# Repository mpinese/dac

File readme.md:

# Note

This project is still under active design, and is not yet completed! Do not build it expecting a functional device... yet.

# An (Almost) No Compromise USB Stereo DAC

This project describes the hardware and firmware for a high-quality DIY USB stereo digital to analogue converter (DAC) with optional integrated digital volume control and headphone amplifier.

## Background

I was after a DAC for my computer headphone setup. Seeing as I enjoy a bit of DIY hardware, I thought to have a go at designing the ideal DAC for me. This would be a high-quality but fairly compact single-box DAC, with integrated preamp and headphone amplifier. If stereo line out and digital (eg S/PDIF in) could be included with minimal effort that would be a bonus.

## Design philosophy

The design is balanced towards maximum audio quality while hopefully avoiding audiophile silliness. Close attention is paid to performance of the key components, gain structure, power rails, stability, and transfer characteristics in the 20-20kHz spectrum. However, you won't see esoteric components, valves, absurdly overspecified linear power supplies / space heaters, etc.

Key principles in the design were:
1. Use asynchronous mode USB audio. I want the PC to have as little influence as possible on the audio playback.
2. Keep the signal digital for as long as possible. For example, perform volume control digitally, rather than using an analogue attenuation stage, which can introduce issues with rolloff and noise.
3. Maintain a simple and clean analog signal path, ideally DC-coupled.
4. Have a solid justification for each design decision; try and avoid reflexive overkill approaches.
5. Where suitable, source components from the [JLCPCB SMT parts library](https://jlcpcb.com/parts/componentSearch). This is a practical and cost-saving measure that is well-worth it for non-critical things like pull-up resistors and decoupling caps.
6. Keep cost under control. Only use high-cost components if lower-cost alternatives are unsuitable.

I would have liked to add '0. Test everything, remove anything unnecessary' but unfortuantely I do not have the kind of test equipment needed to really challenge the design. Therefore some design choices, for example the supply decoupling or separate PSU enclosure, feel a bit over-the-top and can probably be optimised.

## Architecture

```
                                     Panel controls
                                           |
                                           v
                                     +--- MCU ---+
                                     |           |
                                     v           v
  Computer  -->  USB to I2S  -->  Receiver -->  DAC  -->  I2V  -->  Amplifier  -->  Headphones
                                  and ASRC                 |
                                     ^                     v
                                     |                  Line out
                                 Digital in            (3.472 Vpp)
```

* USB to I2S: [Amanero module](https://amanero.com/). A well-established solution for asynchronous USB to I2S conversion. I considered adopting a DIY approach for this stage, but there's no way I could replicate the Amanero's functionality without an investment of effort that far exceeds the cost of the module.
* Clock: Onboard 24.576 MHz oscillator driving both the ASRC and the DAC. The Amanero MCLK output is not used. Simulations indicated that the Kyocera ### is good enough here, and that the popular Crystek CHD series crystal, which has better specs but costs 10X more, is overkill.
* Receiver and ASRC: SRC4392, converting input to fs=96 kHz. This stage also performs digital volume control / attenuation if required.
* DAC: PCM1792A running at fs=96 kHz, with slow rolloff reconstruction filter.
* I2V: Op-amp based, standard Philips architecture of dual transimpedance amplifiers followed by a difference stage. OPA1612 devices for minimum noise. Gain flat within 0.1 dB 20 Hz to 20 kHz. Phase linear within 5 deg to 20 kHz (group delay < 0.1 ms). Total noise < 700 nV RMS (20 Hz - 20 kHz), equivalent to -125 dB relative to +4 dBu output level.
* Amplifier: OPA1612 + LME49600 buffer in feedback loop, unity gain (therefore maximum output level is 3.472 Vpp, matching the line out). AC-coupled input to avoid headphone damage in the case of DC signal, -3 dB at 7.7 Hz, -0.6 dB at 20 Hz, -0.1 dB at 50 Hz and higher; group delay 2.6 ms at 20 Hz, < 0.5 ms at 50 Hz and higher.  Somewhat overkill: characterised down to 16 ohm headphones, stable for all reasonable capacitances, and should be capable of driving any dynamic headphone or IEM out there.
* MCU: STM8S003F3P
* PSU: Switchmode modules for analog and digital supplies, in an external enclosure with LC filtering. In the main DAC enclosure, TPS7A linear postregulators for analog rails.

## Capabilities

* USB input: 
* Digital input: 
* Headphone output: 

## Options

The design is modular and modules can be left out to cut costs or change functionality.  The main modules are:

### Core DAC: essential

This is the only required module.  It performs USB --> stereo analog conversion.

#### Line out startup mute: optional

This module mutes the stereo output while the power rails are unstable (eg during startup).  It prevents the "thump" noise that can often happen when switching the DAC on or off.  However this may not be required in some configurations.

To disable this module, leave out components: 

### Volume control: optional (though highly recommended if headphones are used)

To disable this module, bridge ###

### Headphone amplifier: optional

Components: 

#### Headphone startup mute: optional

Components: 

## Licence

Hardware designs (schematics, PCB layouts, and enclosure plans), software, and documentation are licensed for reuse under the Creative Commons Attribution 4.0 Licence (CC BY 4.0). For more details on this licence, visit https://creativecommons.org/licenses/by/4.0/.

Component models (3D and 2D) under the design/pcbs/lib directory, and simulation models (`*.s*p`, `*.lib`, `*.tld`, `*.TSM` under the simulations directory) remain the property of their creators and are not covered by this CC BY 4.0 licence.

The Kicad BOM template bom2grouped_csv_jlcpcb.xsl was created bt arturo182, see https://gist.github.com/arturo182/a8c4a4b96907cfccf616a1edb59d0389.

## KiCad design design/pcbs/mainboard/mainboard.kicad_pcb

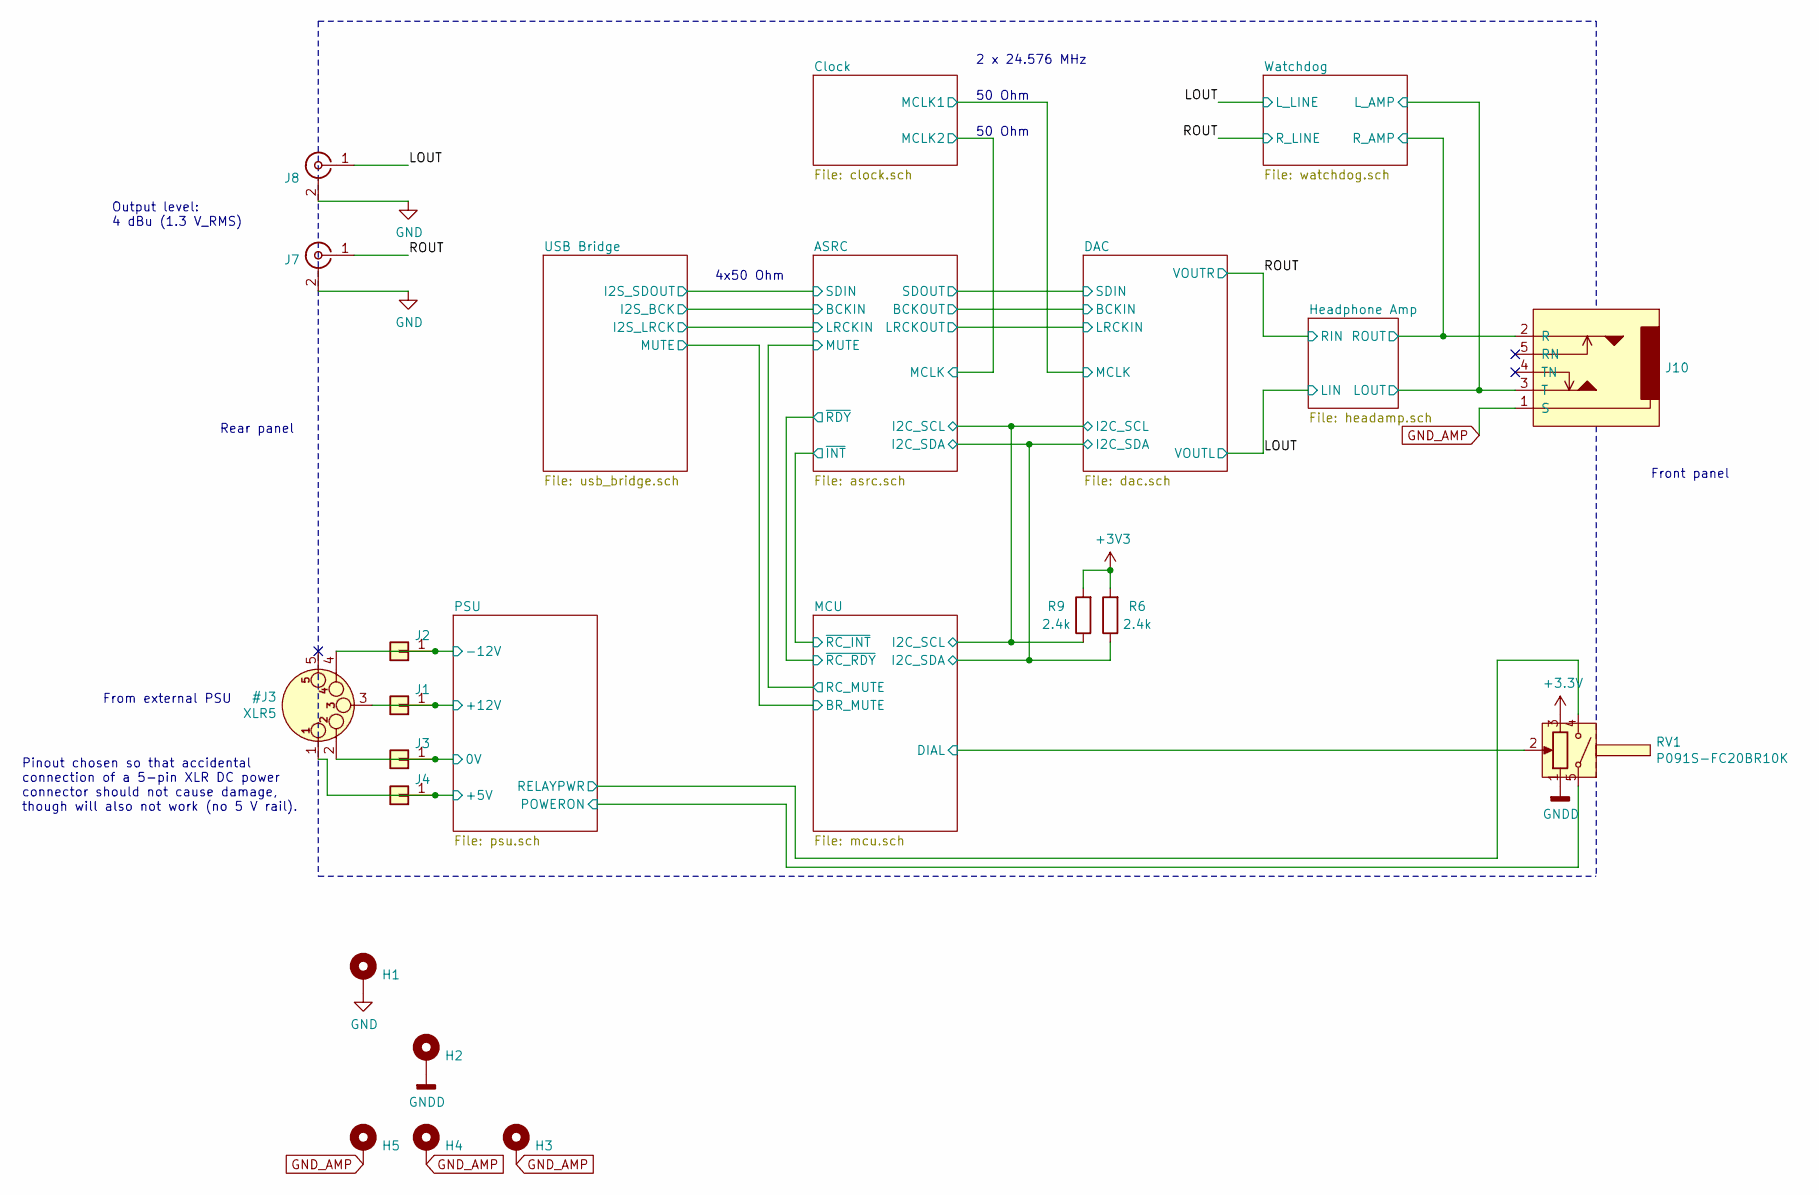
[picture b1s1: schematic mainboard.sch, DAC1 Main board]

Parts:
H1, H2, H3, H4, H5: MountingHole; MountingHole_3.2mm_M3_Pad_Via
J1, J2, J3, J4: Conn_01x01; SolderWirePad_1x01_Drill1.5mm
J7: Conn_Coaxial; SolderWirePad_1x02_P5.08mm_Drill1.5mm; DigiKey SC1828-ND
J8: Conn_Coaxial; SolderWirePad_1x02_P5.08mm_Drill1.5mm; DigiKey SC2440-ND
J10: AudioJackSw; Amphenol_ACJS-MHOM; DigiKey 889-1818-ND
R6, R9: 2.4k; R_0402_1005Metric; LCSC C25882
RV1: P091S-FC20BR10K; DigiKey 987-1283-ND

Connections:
/ASRC/I2C_SCL: R9.1; also elsewhere on the board
/ASRC/I2C_SDA: R6.1; also elsewhere on the board
/Headphone Amp/LOUT: J10.3 (T); also elsewhere on the board
/Headphone Amp/ROUT: J10.2 (R); also elsewhere on the board
/LOUT: J8.1 (In); also elsewhere on the board
/MCU/DIAL: RV1.2; also elsewhere on the board
/PSU/POWERON: RV1.5; also elsewhere on the board
/ROUT: J7.1 (In); also elsewhere on the board
GNDD: H2.1, RV1.1; also elsewhere on the board
GND_AMP: H3.1, H4.1, H5.1, J10.1 (S), J10.6 (S); also elsewhere on the board

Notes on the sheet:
50 Ohm
2 x 24.576 MHz
From external PSU
Rear panel
Front panel
Pinout chosen so that accidental connection of a 5-pin XLR DC power connector should not cause damage, though will also not work (no 5 V rail).
Output level: 4 dBu (1.3 V_RMS)
4x50 Ohm

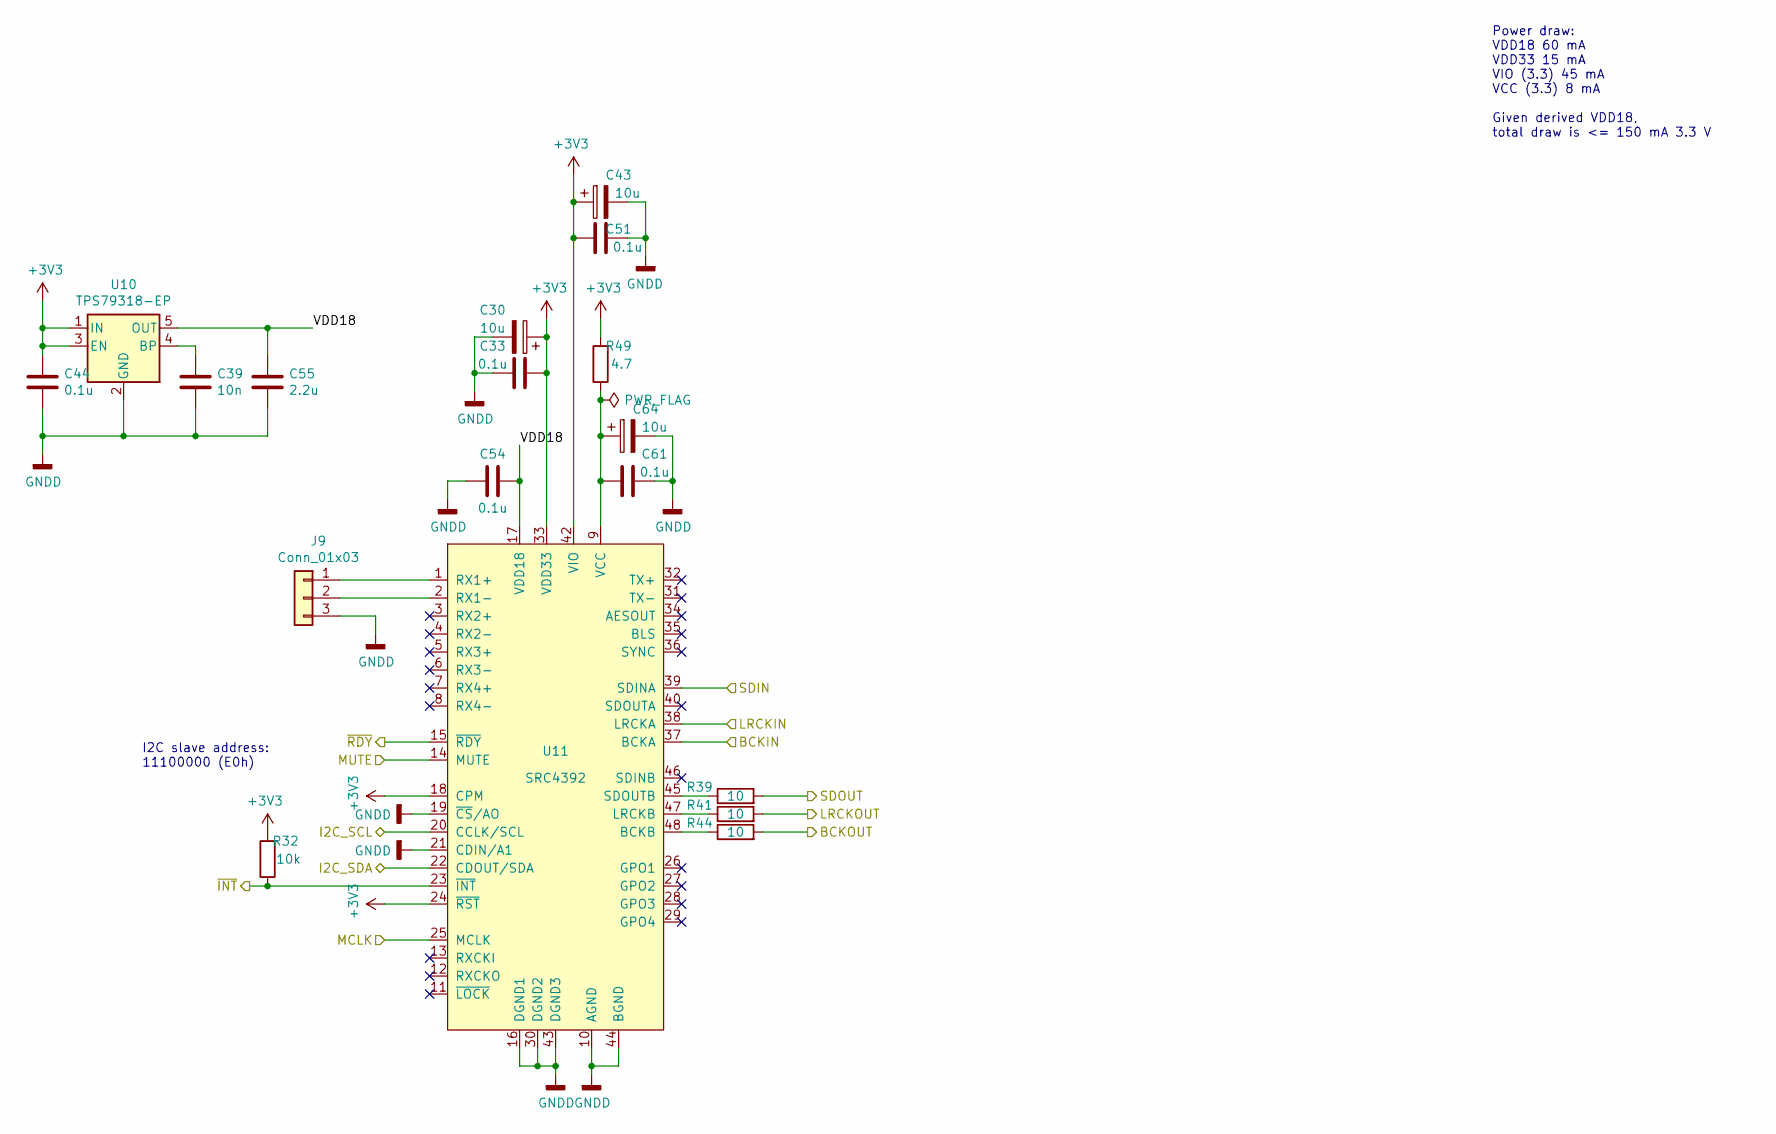
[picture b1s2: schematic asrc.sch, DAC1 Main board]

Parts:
C30, C43, C64: 10u; CP_EIA-3216-18_Kemet-A; LCSC C7171
C33, C44, C51, C54, C61: 0.1u; C_0603_1608Metric; LCSC C14663
C39: 10n; C_0402_1005Metric; LCSC C15195
C55: 2.2u; C_0603_1608Metric; LCSC C23630
J9: Conn_01x03; PinHeader_1x03_P2.54mm_Vertical
R32: 10k; R_0402_1005Metric; LCSC C25744
R39, R41, R44: 10; R_0402_1005Metric; LCSC C25077
R49: 4.7; R_0603_1608Metric; DigiKey 408-1436-1-ND
U10: TPS79318-EP; SOT-23-5; DigiKey 296-12155-1-ND
U11: SRC4392; TQFP-48_7x7mm_P0.5mm; DigiKey 296-19740-1-ND

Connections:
/ASRC/BCKIN: U11.37 (BCKA); also elsewhere on the board
/ASRC/I2C_SCL: U11.20 (CCLK/SCL); also elsewhere on the board
/ASRC/I2C_SDA: U11.22 (CDOUT/SDA); also elsewhere on the board
/ASRC/MCLK: U11.25 (MCLK); also elsewhere on the board
/ASRC/MUTE: U11.14 (MUTE); also elsewhere on the board
/ASRC/VDD18: C54.1, C55.1, U10.5 (OUT), U11.17 (VDD18)
/ASRC/~INT: R32.1, U11.23 (~INT); also elsewhere on the board
/DAC/BCKIN: R44.2; also elsewhere on the board
/DAC/LRCKIN: R41.2; also elsewhere on the board
/DAC/SDIN: R39.2; also elsewhere on the board
/MCU/~RC_RDY: U11.15 (~RDY); also elsewhere on the board
/USB Bridge/I2S_LRCK: U11.38 (LRCKA); also elsewhere on the board
/USB Bridge/I2S_SDOUT: U11.39 (SDINA); also elsewhere on the board
GNDD: C30.2, C33.2, C39.2, C43.2, C44.2, C51.2, C54.2, C55.2, C61.1, C64.2, J9.3, U10.2 (GND), U11.10 (AGND), U11.16 (DGND1), U11.19 (~CS~/AO), U11.21 (CDIN/A1), U11.30 (DGND2), U11.43 (DGND3), U11.44 (BGND); also elsewhere on the board
unnamed: C39.1, U10.4 (BP)
unnamed: C61.2, C64.1, R49.1, U11.9 (VCC)
unnamed: J9.1, U11.1 (RX1+)
unnamed: J9.2, U11.2 (RX1-)
unnamed: R39.1, U11.45 (SDOUTB)
unnamed: R41.1, U11.47 (LRCKB)
unnamed: R44.1, U11.48 (BCKB)

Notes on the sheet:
I2C slave address: 11100000 (E0h)
Power draw: VDD18 60 mA VDD33 15 mA VIO (3.3) 45 mA VCC (3.3) 8 mA Given derived VDD18, total draw is <= 150 mA 3.3 V

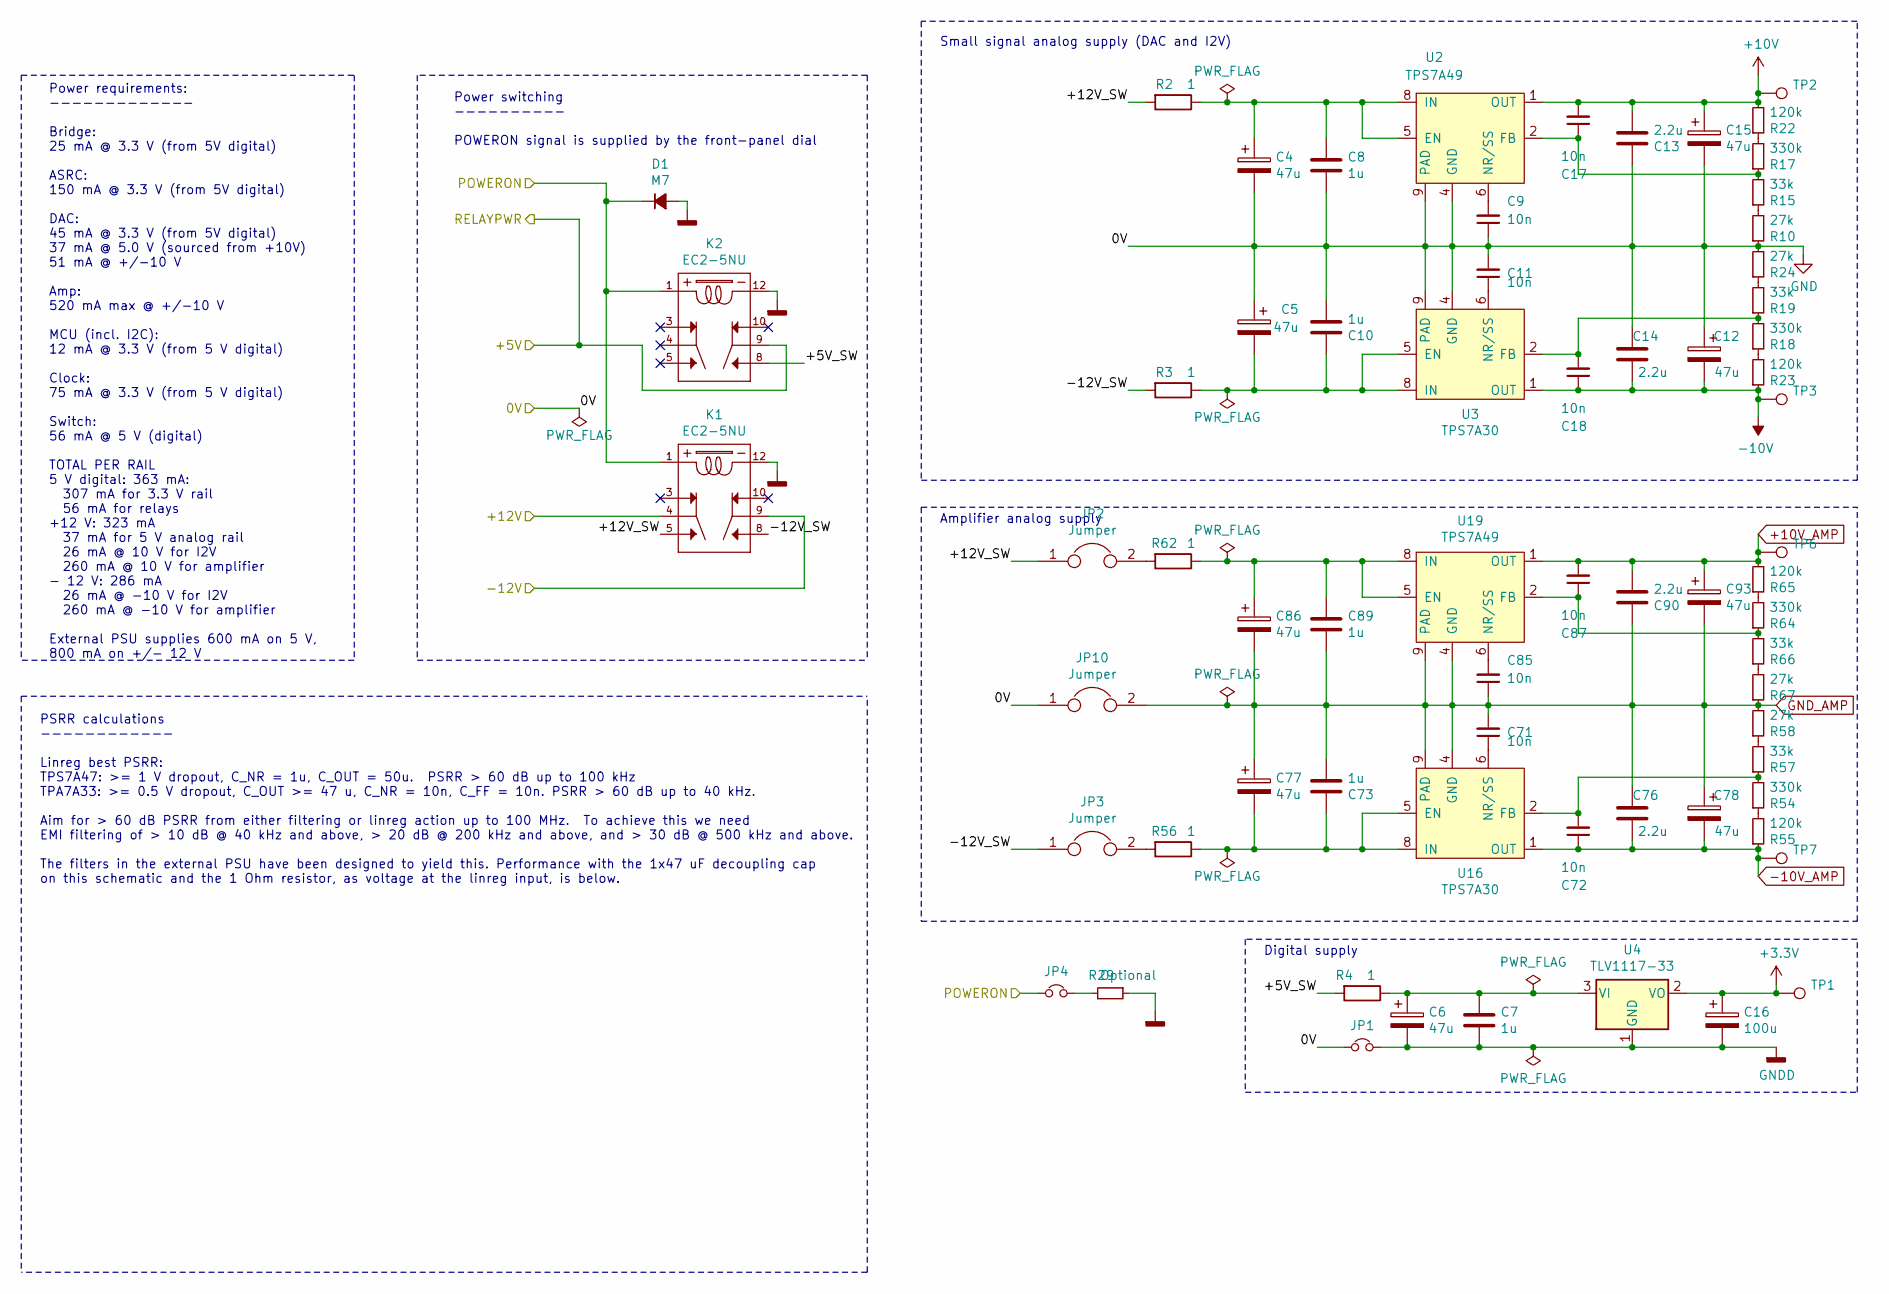
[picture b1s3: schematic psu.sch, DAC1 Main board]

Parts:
C4, C5, C6, C12, C15, C77, C78, C86, C93: 47u; CP_Radial_D8.0mm_P3.50mm; DigiKey 732-6324-1-ND
C7, C8, C10, C73, C89: 1u; C_0805_2012Metric; LCSC C28323
C9, C11, C17, C18, C71, C72, C85, C87: 10n; C_0603_1608Metric; LCSC C14663
C13, C14, C76, C90: 2.2u; C_1206_3216Metric; LCSC C50254
C16: 100u; CP_Radial_D8.0mm_P3.50mm; DigiKey 1572-1662-ND
D1: M7; D_SOD-123F; LCSC C64898
JP1: Jumper_NC_Small; SolderJumper-2_P1.3mm_Bridged2Bar_Pad1.0x1.5mm
JP2, JP3: Jumper; PinHeader_1x02_P2.54mm_Vertical
JP4: PinHeader_1x02_P2.54mm_Vertical
JP10: Jumper; SolderJumper-2_P1.3mm_Bridged2Bar_Pad1.0x1.5mm
K1, K2: EC2-5NU; RELAY_EC2-5NU; DigiKey 399-11052-5-ND
R2, R3, R4, R56, R62: 1; R_1206_3216Metric; LCSC C17928
R10, R24, R58, R67: 27k; R_0402_1005Metric; LCSC C25771
R15, R19, R57, R66: 33k; R_0402_1005Metric; LCSC C25779
R17, R18, R54, R64: 330k; R_0402_1005Metric; LCSC C25778
R22, R23, R55, R65: 120k; R_0402_1005Metric; LCSC C25750
R29: Optional; R_Axial_DIN0204_L3.6mm_D1.6mm_P5.08mm_Horizontal
TP1, TP2, TP3, TP6, TP7: TestPoint; TestPoint_THTPad_D3.0mm_Drill1.5mm
U2, U19: TPS7A49; MSOP-8-1EP_3x3mm_P0.65mm_EP1.68x1.88mm_ThermalVias; DigiKey 296-27751-1-ND
U3, U16: TPS7A30; MSOP-8-1EP_3x3mm_P0.65mm_EP1.68x1.88mm_ThermalVias; DigiKey 296-27750-1-ND
U4: TLV1117-33; SOT-223-3_TabPin2; DigiKey 296-28778-1-ND

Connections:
+10V: C13.2, C15.1, C17.2, R22.2, TP2.1, U2.1 (OUT); also elsewhere on the board
+10V_AMP: C87.2, C90.2, C93.1, R65.2, TP6.1, U19.1 (OUT); also elsewhere on the board
-10V: C12.2, C14.2, C18.1, R23.1, TP3.1, U3.1 (OUT); also elsewhere on the board
-10V_AMP: C72.1, C76.2, C78.2, R55.1, TP7.1, U16.1 (OUT); also elsewhere on the board
/PSU/+5V_SW: K2.8, R4.2
/PSU/+12V_SW: JP2.1, K1.5, R2.2
/PSU/-12V_SW: JP3.1, K1.8, R3.2
/PSU/POWERON: D1.1 (K), JP4.1, K1.1, K2.1; also elsewhere on the board
GNDD: C6.2, C7.2, C16.2, D1.2 (A), JP1.2, K1.12, K2.12, R29.1, U4.1 (GND); also elsewhere on the board
GND_AMP: C71.2, C73.2, C76.1, C77.1, C78.1, C85.1, C86.2, C89.2, C90.1, C93.2, JP10.2, R58.2, R67.1, U16.4 (GND), U16.9 (PAD), U19.4 (GND), U19.9 (PAD); also elsewhere on the board
unnamed: C4.1, C8.1, R2.1, U2.5 (EN), U2.8 (IN)
unnamed: C6.1, C7.1, R4.1, U4.3 (VI)
unnamed: C9.2, U2.6 (NR/SS)
unnamed: C5.2, C10.1, R3.1, U3.5 (EN), U3.8 (IN)
unnamed: C11.1, U3.6 (NR/SS)
unnamed: C17.1, R15.2, R17.1, U2.2 (FB)
unnamed: C18.2, R18.2, R19.1, U3.2 (FB)
unnamed: C71.1, U16.6 (NR/SS)
unnamed: C72.2, R54.2, R57.1, U16.2 (FB)
unnamed: C73.1, C77.2, R56.1, U16.5 (EN), U16.8 (IN)
unnamed: C85.2, U19.6 (NR/SS)
unnamed: C86.1, C89.1, R62.1, U19.5 (EN), U19.8 (IN)
unnamed: C87.1, R64.1, R66.2, U19.2 (FB)
unnamed: JP2.2, R62.2
unnamed: JP3.2, R56.2
unnamed: JP4.2, R29.2
unnamed: R10.2, R15.1
unnamed: R17.2, R22.1
unnamed: R18.1, R23.2
unnamed: R19.2, R24.1
unnamed: R54.1, R55.2
unnamed: R57.2, R58.1
unnamed: R64.2, R65.1
unnamed: R66.1, R67.2

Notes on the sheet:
PSRR calculations ------------ Linreg best PSRR: TPS7A47: >= 1 V dropout, C_NR = 1u, C_OUT = 50u. PSRR > 60 dB up to 100 kHz TPA7A33: >= 0.5 V dropout, C_OUT >= 47 u, C_NR = 10n, C_FF = 10n. PSRR > 60 dB up to 40 kHz. Aim for > 60 dB PSRR from either filtering or linreg action up to 100 MHz. To ach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
Power switching ---------- POWERON signal is supplied by the front-panel dial
Power requirements: ------------- Bridge: 25 mA @ 3.3 V (from 5V digital) ASRC: 150 mA @ 3.3 V (from 5V digital) DAC: 45 mA @ 3.3 V (from 5V digital) 37 mA @ 5.0 V (sourced from +10V) 51 mA @ +/-10 V Amp: 520 mA max @ +/-10 V MCU (incl. I2C): 12 mA @ 3.3 V (from 5 V digital) Clock: 75 mA @ 3.3 V (f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
Small signal analog supply (DAC and I2V)
Amplifier analog supply
Digital supply

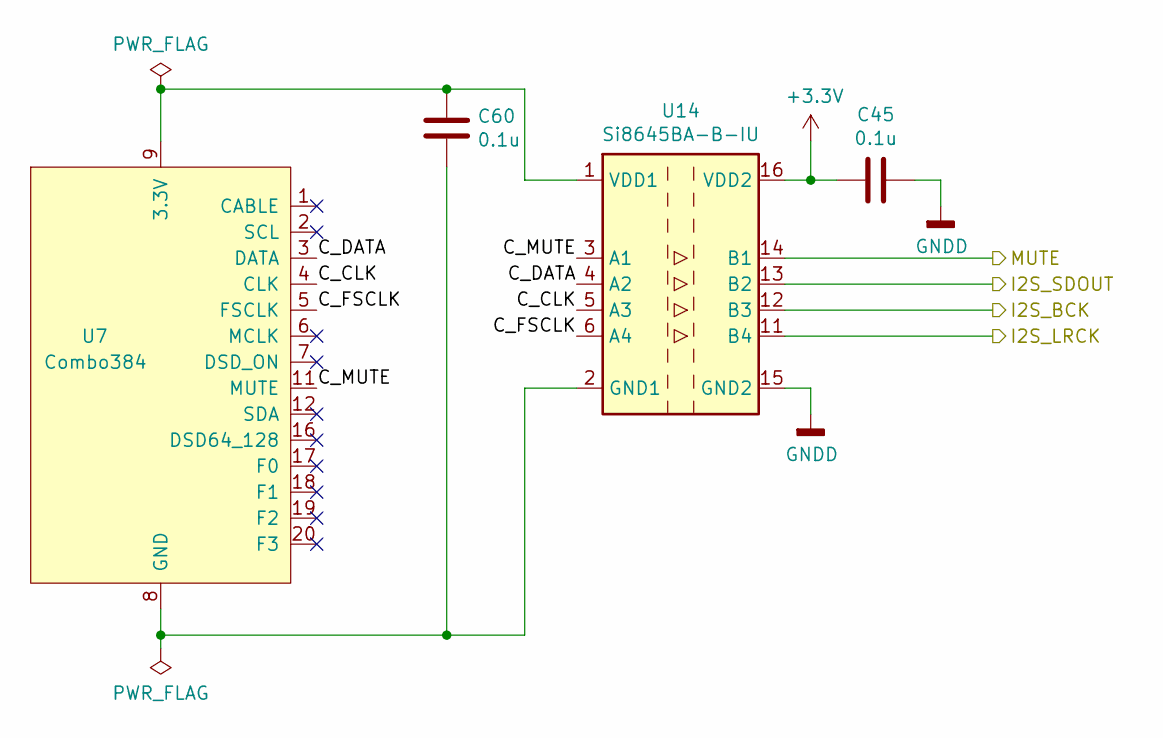
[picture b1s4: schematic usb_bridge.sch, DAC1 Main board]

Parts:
C45, C60: 0.1u; C_0603_1608Metric; LCSC C14663
U7: Combo384; AmaneroCombo384
U14: Si8645BA-B-IU; QSOP-16_3.9x4.9mm_P0.635mm; DigiKey 336-2096-5-ND

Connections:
/ASRC/BCKIN: U14.12 (B3); also elsewhere on the board
/MCU/BR_MUTE: U14.14 (B1); also elsewhere on the board
/USB Bridge/C_CLK: U7.4 (CLK), U14.5 (A3)
/USB Bridge/C_DATA: U7.3 (DATA), U14.4 (A2)
/USB Bridge/C_FSCLK: U7.5 (FSCLK), U14.6 (A4)
/USB Bridge/C_MUTE: U7.11 (MUTE), U14.3 (A1)
/USB Bridge/I2S_LRCK: U14.11 (B4); also elsewhere on the board
/USB Bridge/I2S_SDOUT: U14.13 (B2); also elsewhere on the board
GNDD: C45.1, U14.9 (GND2), U14.15 (GND2); also elsewhere on the board
unnamed: C60.1, U7.9 (3.3V), U7.10 (3.3V), U14.1 (VDD1)
unnamed: C60.2, U7.8 (GND), U7.13 (GND), U7.14 (GND), U7.15 (GND), U14.2 (GND1), U14.8 (GND1)

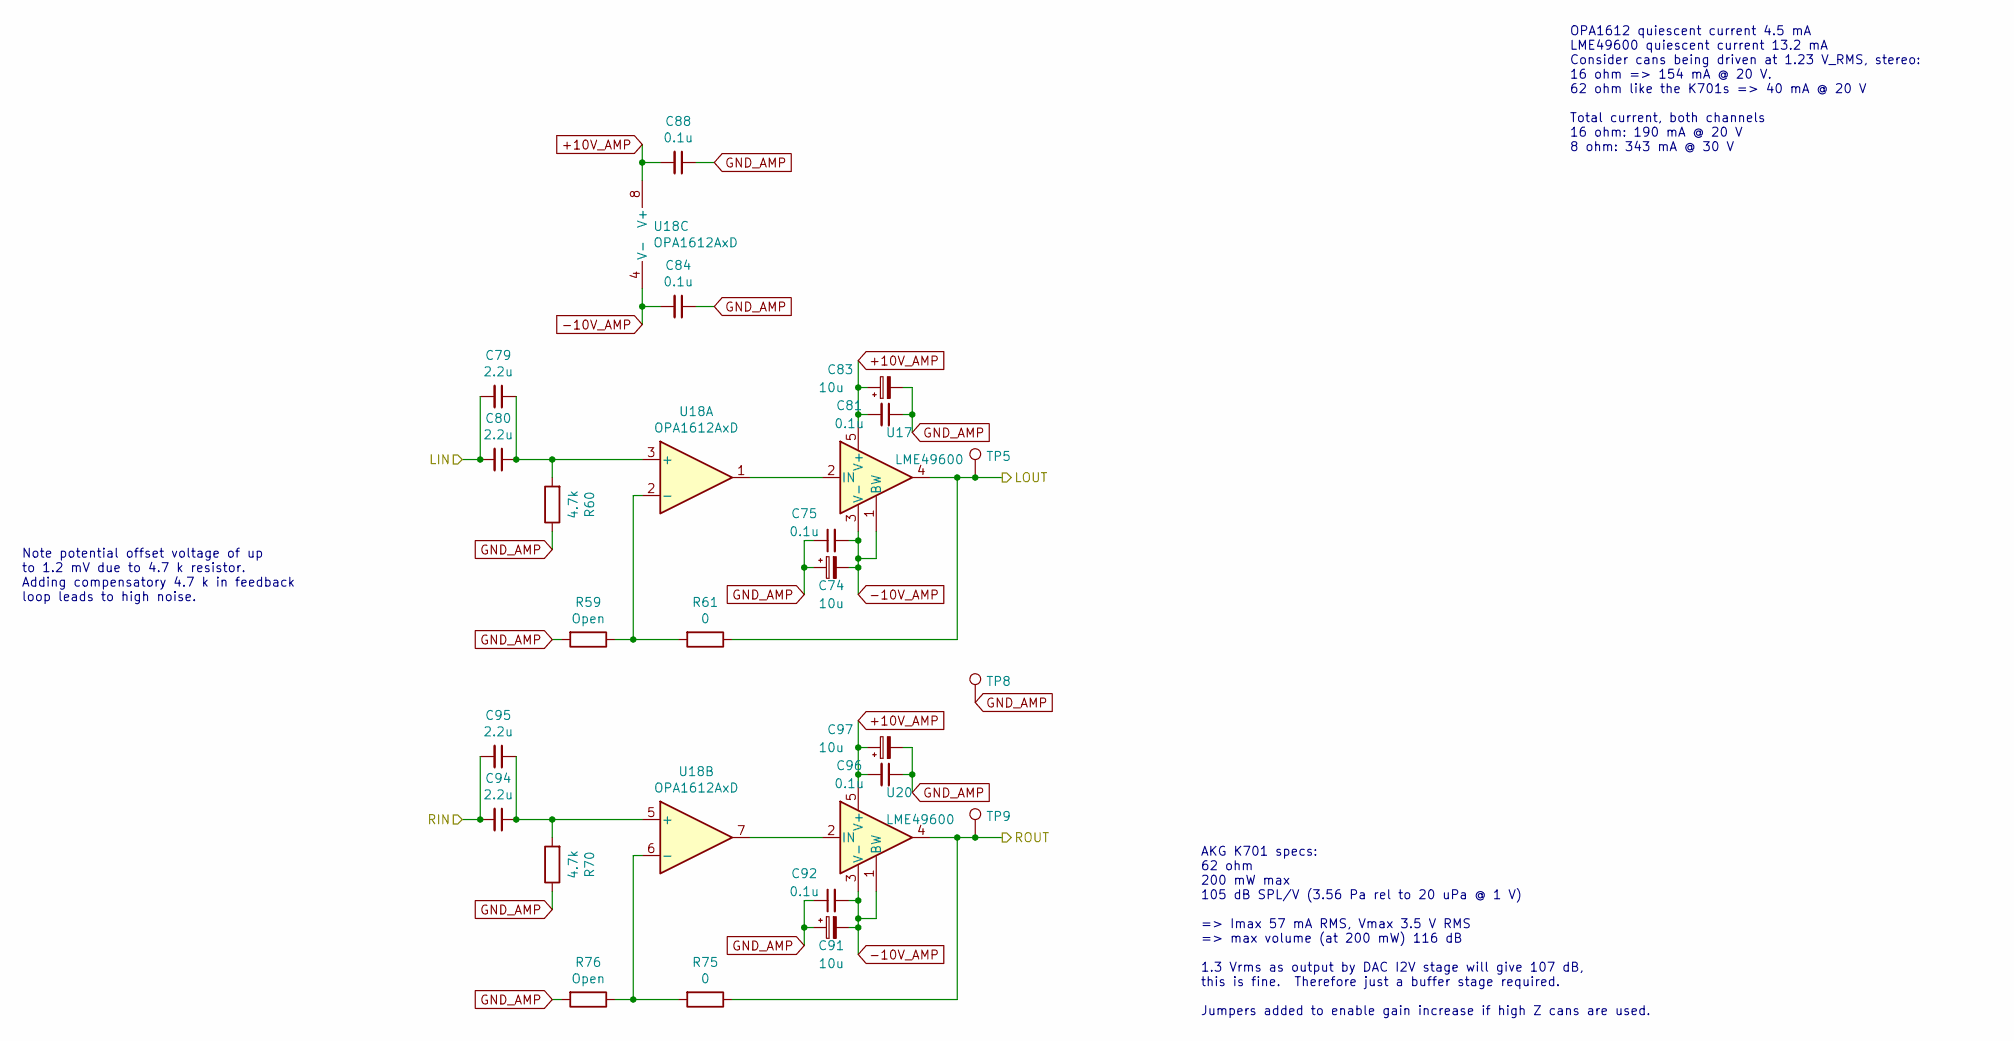
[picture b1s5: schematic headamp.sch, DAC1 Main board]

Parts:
C74, C83, C91, C97: 10u; CP_EIA-3216-18_Kemet-A; LCSC C7171
C75, C81, C84, C88, C92, C96: 0.1u; C_0603_1608Metric; LCSC C14663
C79, C80, C94, C95: 2.2u; C_Rect_L18.0mm_W11.0mm_P15.00mm_FKS3_FKP3; DigiKey 732-11840-ND
R59, R76: Open; R_Axial_DIN0207_L6.3mm_D2.5mm_P10.16mm_Horizontal
R60, R70: 4.7k; R_0603_1608Metric; DigiKey RG16P4.7KBCT-ND
R61, R75: 0; R_Axial_DIN0207_L6.3mm_D2.5mm_P10.16mm_Horizontal
TP5, TP8, TP9: TestPoint; TestPoint_THTPad_D3.0mm_Drill1.5mm
U17, U20: LME49600; TO-263-5_TabPin3; DigiKey 296-43968-5-ND
U18: OPA1612AxD; SOIC-8_3.9x4.9mm_P1.27mm; DigiKey 296-39098-1-ND

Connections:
+10V_AMP: C81.2, C83.1, C88.2, C96.2, C97.1, U17.5 (V+), U18.8 (V+), U20.5 (V+); also elsewhere on the board
-10V_AMP: C74.2, C75.2, C84.2, C91.2, C92.2, U17.1 (BW), U17.3 (V-), U18.4 (V-), U20.1 (BW), U20.3 (V-); also elsewhere on the board
/Headphone Amp/LOUT: R61.1, TP5.1, U17.4; also elsewhere on the board
/Headphone Amp/ROUT: R75.1, TP9.1, U20.4; also elsewhere on the board
/LOUT: C79.2, C80.2; also elsewhere on the board
/ROUT: C94.2, C95.2; also elsewhere on the board
GND_AMP: C74.1, C75.1, C81.1, C83.2, C84.1, C88.1, C91.1, C92.1, C96.1, C97.2, R59.2, R60.1, R70.1, R76.2, TP8.1; also elsewhere on the board
unnamed: C79.1, C80.1, R60.2, U18.3 (+)
unnamed: C94.1, C95.1, R70.2, U18.5 (+)
unnamed: R59.1, R61.2, U18.2 (-)
unnamed: R75.2, R76.1, U18.6 (-)
unnamed: U17.2 (IN), U18.1
unnamed: U18.7, U20.2 (IN)

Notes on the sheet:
AKG K701 specs: 62 ohm 200 mW max 105 dB SPL/V (3.56 Pa rel to 20 uPa @ 1 V) => Imax 57 mA RMS, Vmax 3.5 V RMS => max volume (at 200 mW) 116 dB 1.3 Vrms as output by DAC I2V stage will give 107 dB, this is fine. Therefore just a buffer stage required. Jumpers added to enable gain increase if high Z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
OPA1612 quiescent current 4.5 mA LME49600 quiescent current 13.2 mA Consider cans being driven at 1.23 V_RMS, stereo: 16 ohm => 154 mA @ 20 V. 62 ohm like the K701s => 40 mA @ 20 V Total current, both channels 16 ohm: 190 mA @ 20 V 8 ohm: 343 mA @ 30 V
Note potential offset voltage of up to 1.2 mV due to 4.7 k resistor. Adding compensatory 4.7 k in feedback loop leads to high noise.

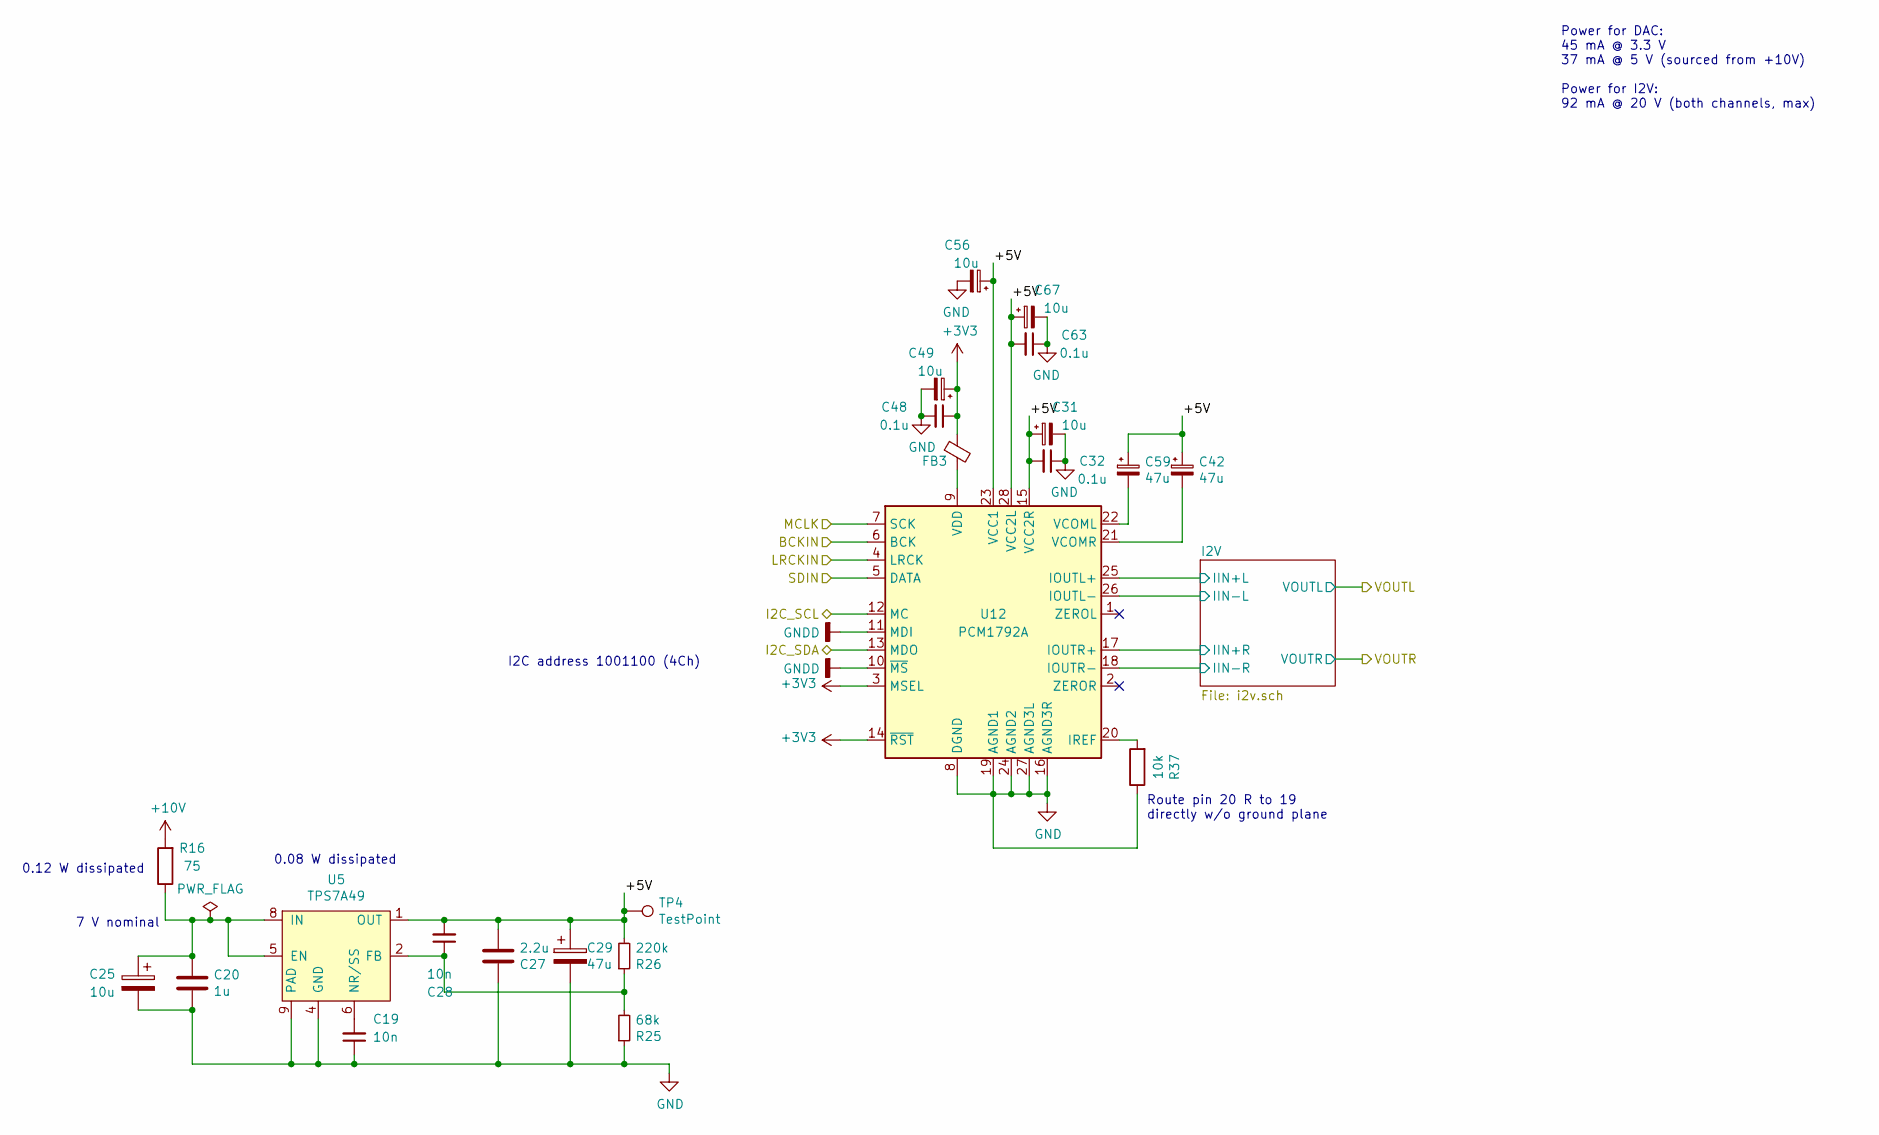
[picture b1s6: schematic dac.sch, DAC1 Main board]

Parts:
C19, C28: 10n; C_0603_1608Metric; LCSC C14663
C20: 1u; C_0805_2012Metric; LCSC C28323
C25, C31, C49, C56, C67: 10u; CP_EIA-3216-18_Kemet-A; LCSC C7171
C27: 2.2u; C_1206_3216Metric; LCSC C50254
C29: 47u; CP_Radial_D5.0mm_P2.00mm; DigiKey 732-9306-1-ND
C32, C48, C63: 0.1u; C_0603_1608Metric; LCSC C14663
C42, C59: 47u; CP_Radial_D6.3mm_P2.50mm; DigiKey 493-15014-ND
FB3: Ferrite_Bead_Small; R_0603_1608Metric_Pad1.05x0.95mm_HandSolder
R16: 75; R_1206_3216Metric; LCSC C17985
R25: 68k; R_0402_1005Metric; LCSC C36871
R26: 220k; R_0402_1005Metric; LCSC C25767
R37: 10k; R_0402_1005Metric; DigiKey RG10P10.0KDCT-ND
TP4: TestPoint; TestPoint_THTPad_D3.0mm_Drill1.5mm
U5: TPS7A49; MSOP-8-1EP_3x3mm_P0.65mm_EP1.68x1.88mm_ThermalVias; DigiKey 296-27751-1-ND
U12: PCM1792A; SSOP-28_5.3x10.2mm_P0.65mm; DigiKey 296-26303-5-ND

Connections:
+10V: R16.2; also elsewhere on the board
/ASRC/I2C_SCL: U12.12 (MC); also elsewhere on the board
/ASRC/I2C_SDA: U12.13 (MDO); also elsewhere on the board
/DAC/+5V: C27.2, C28.2, C29.1, C31.1, C32.2, C42.1, C56.1, C59.1, C63.2, C67.1, R26.2, TP4.1, U5.1 (OUT), U12.15 (VCC2R), U12.23 (VCC1), U12.28 (VCC2L)
/DAC/BCKIN: U12.6 (BCK); also elsewhere on the board
/DAC/I2V/IIN+L: U12.25 (IOUTL+); also elsewhere on the board
/DAC/I2V/IIN+R: U12.17 (IOUTR+); also elsewhere on the board
/DAC/I2V/IIN-L: U12.26 (IOUTL-); also elsewhere on the board
/DAC/I2V/IIN-R: U12.18 (IOUTR-); also elsewhere on the board
/DAC/LRCKIN: U12.4 (LRCK); also elsewhere on the board
/DAC/MCLK: U12.7 (SCK); also elsewhere on the board
/DAC/SDIN: U12.5 (DATA); also elsewhere on the board
GNDD: U12.10 (~MS), U12.11 (MDI); also elsewhere on the board
unnamed: C19.2, U5.6 (NR/SS)
unnamed: C20.1, C25.1, R16.1, U5.5 (EN), U5.8 (IN)
unnamed: C28.1, R25.2, R26.1, U5.2 (FB)
unnamed: C42.2, U12.21 (VCOMR)
unnamed: C59.2, U12.22 (VCOML)
unnamed: FB3.2, U12.9 (VDD)
unnamed: R37.2, U12.20 (IREF)

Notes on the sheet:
Power for DAC: 45 mA @ 3.3 V 37 mA @ 5 V (sourced from +10V) Power for I2V: 92 mA @ 20 V (both channels, max)
I2C address 1001100 (4Ch)
0.08 W dissipated
Route pin 20 R to 19 directly w/o ground plane
0.12 W dissipated
7 V nominal

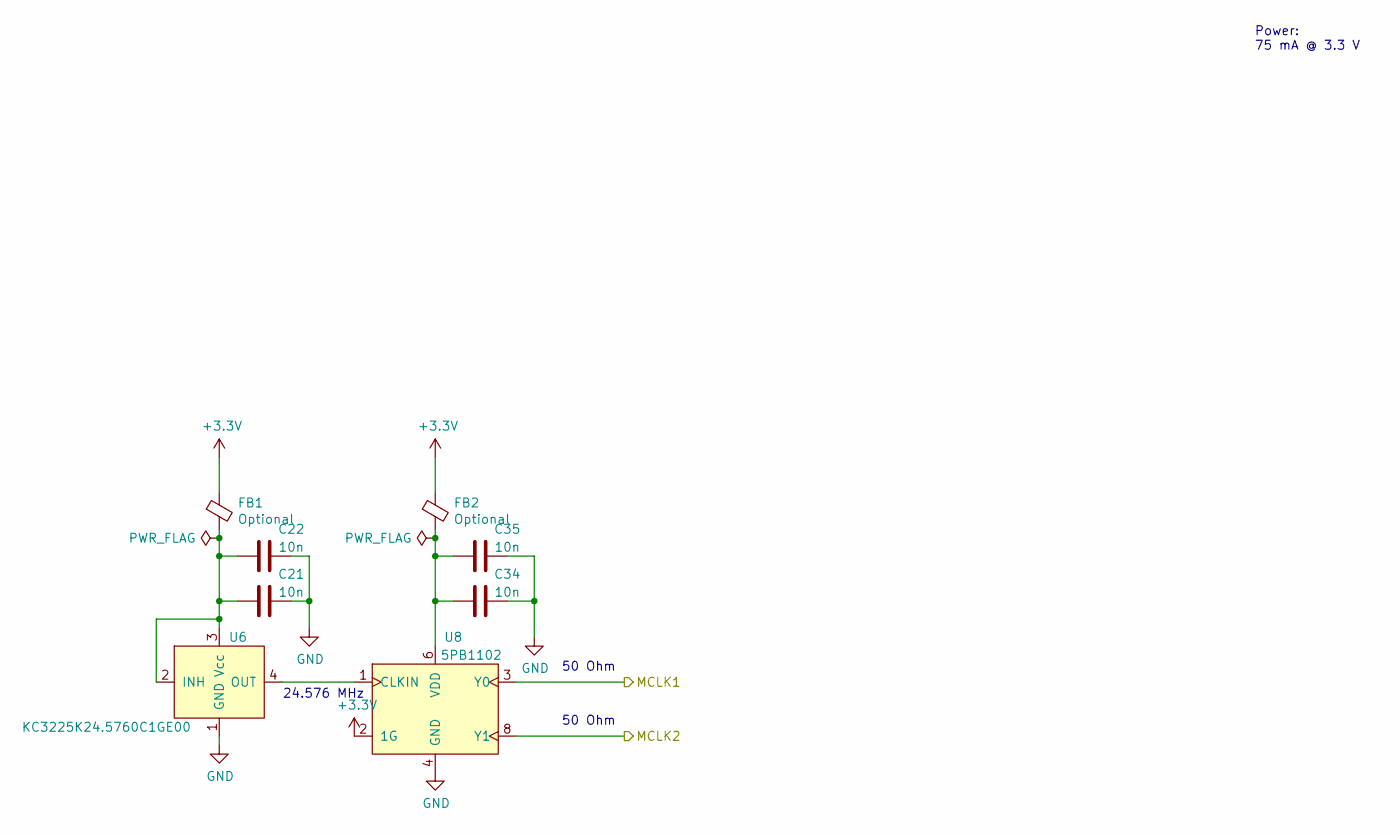
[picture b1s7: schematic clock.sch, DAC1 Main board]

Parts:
C21, C22, C34, C35: 10n; C_0603_1608Metric; LCSC C14663
FB1, FB2: Optional; R_0603_1608Metric_Pad1.05x0.95mm_HandSolder
U6: KC3225K24.5760C1GE00; Crystal_SMD_3225-4Pin_3.2x2.5mm; DigiKey 1253-1407-1-ND
U8: 5PB1102; TSSOP-8_4.4x3mm_P0.65mm; DigiKey 800-2889-5-ND

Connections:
/ASRC/MCLK: U8.8 (Y1); also elsewhere on the board
/DAC/MCLK: U8.3 (Y0); also elsewhere on the board
unnamed: C21.2, C22.2, FB1.2, U6.2 (INH), U6.3 (Vcc)
unnamed: C34.2, C35.2, FB2.2, U8.6 (VDD)
unnamed: U6.4 (OUT), U8.1 (CLKIN)

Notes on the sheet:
24.576 MHz
50 Ohm
Power: 75 mA @ 3.3 V

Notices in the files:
design/pcbs/external_psu/external_psu.kicad_pcb:
© Mark Pinese 2020
To view a copy of this license, visit https://creativecommons.org/licenses/by/4.0
This work is licensed under CC BY 4.0.
Reuse permitted under CC BY 4.0
design/pcbs/mainboard/mainboard.kicad_pcb:
CC BY 4.0
parts and their libraries:
Copyright 2016 Accelerated Designs. All rights reserved.
